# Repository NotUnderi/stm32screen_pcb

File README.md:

# stm32screen

PCB designed to fit into a 52mm closure and interface with some car sensors and stuff

<b>10.6.2026</b>
<br>
Ordered PCBs from JLCPCB. Changed made to previous version pictured below these new ones are disposing of the USB connector entirely and with it, the SP0503BAHTG TVS diode, adding a user switch, Adding better labels on the silkscreen, slightly better layout, disposing of THT caps. The board will be powered straight from the car's battery, this allows easier installation and decreases cost and complexity.

17.3.2026

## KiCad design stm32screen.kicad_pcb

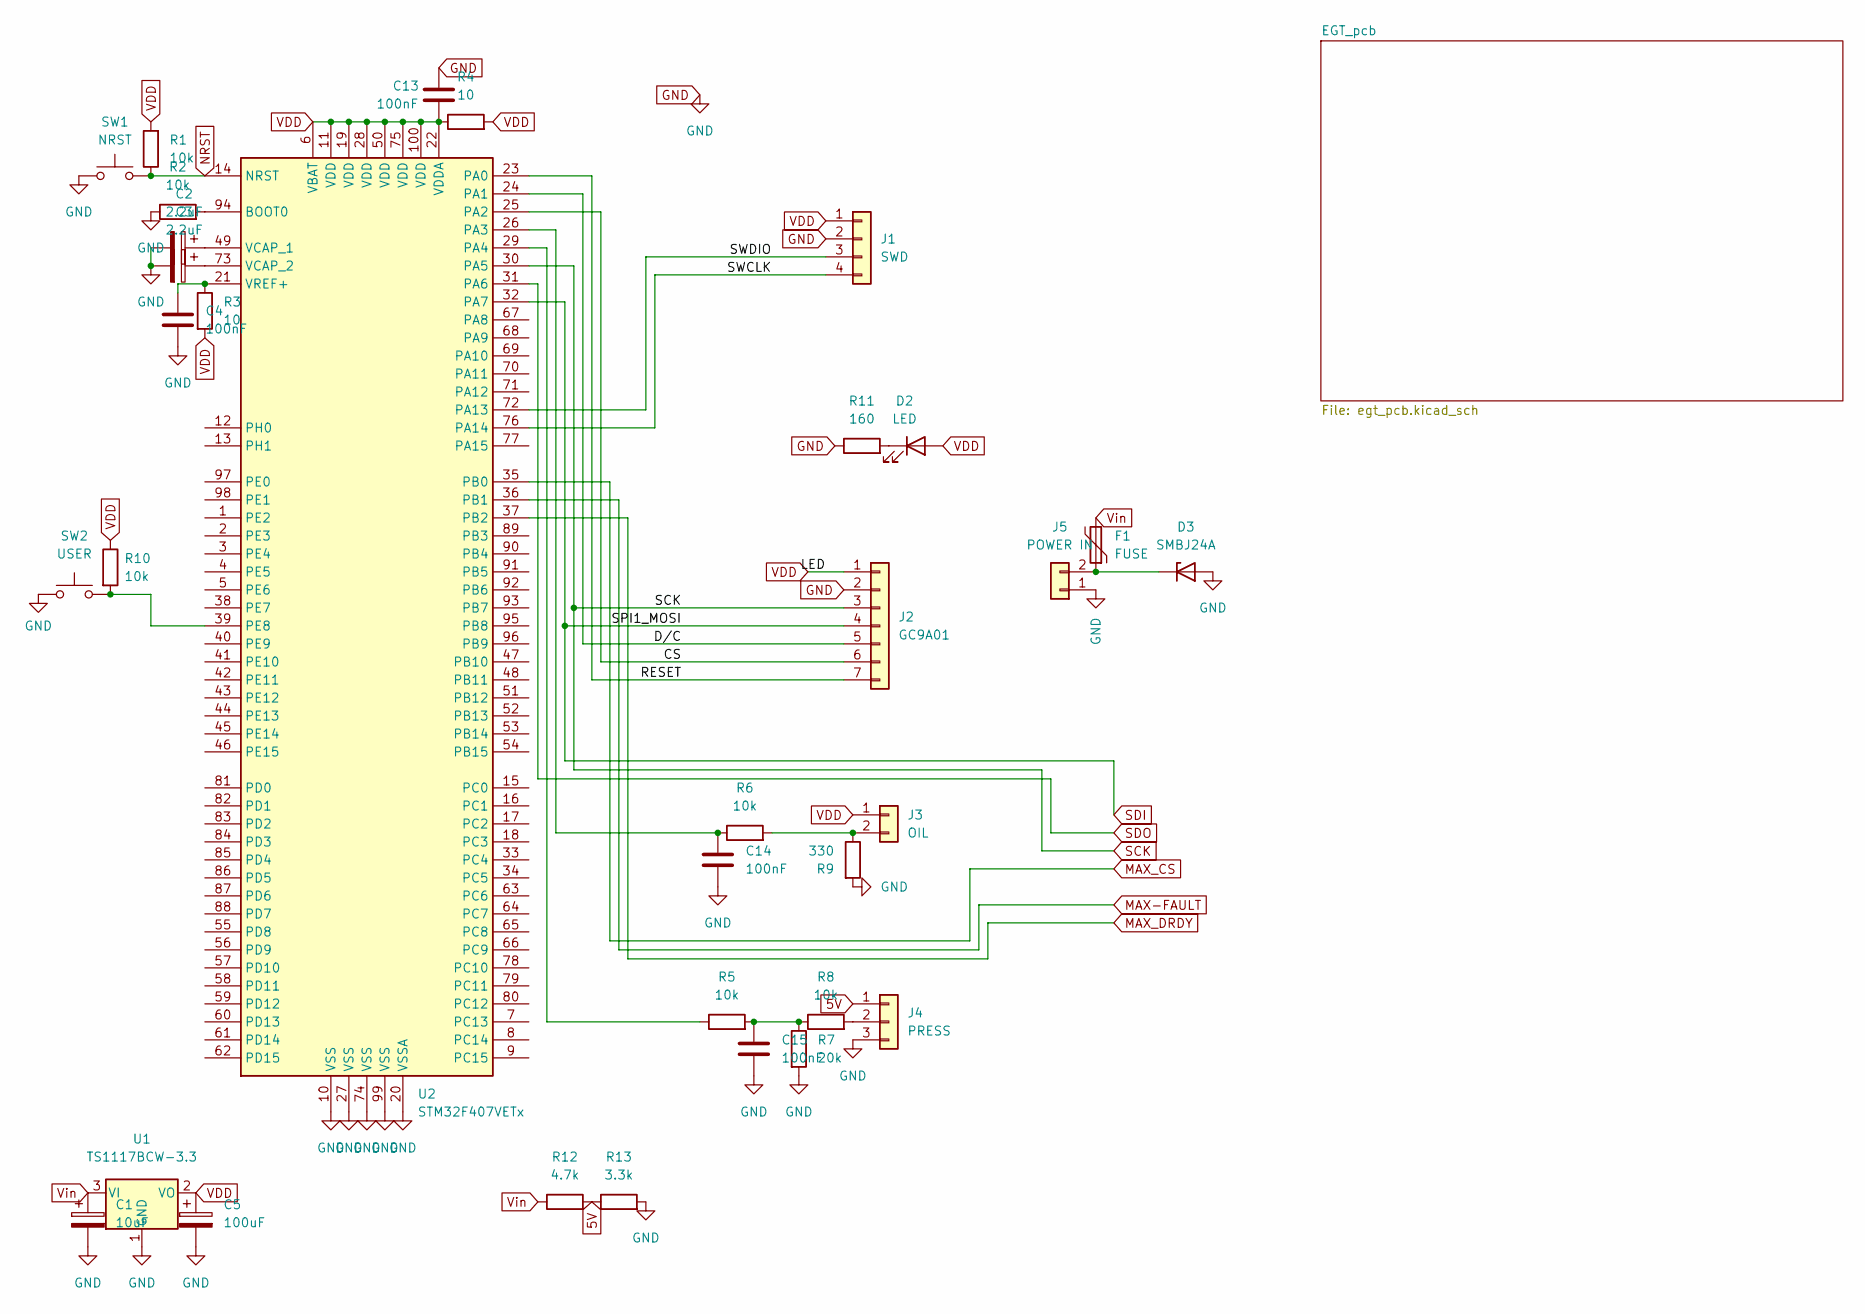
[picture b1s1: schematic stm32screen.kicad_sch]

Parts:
C1: 10uF; C_1210_3225Metric_Pad1.33x2.70mm_HandSolder
C2, C3: 2.2uF; C_1206_3216Metric_Pad1.33x1.80mm_HandSolder
C4, C13, C14, C15: 100nF; C_0805_2012Metric_Pad1.18x1.45mm_HandSolder
C5: 100uF; C_1210_3225Metric_Pad1.33x2.70mm_HandSolder
D2: LED; LED_0603_1608Metric_Pad1.05x0.95mm_HandSolder
D3: SMBJ24A; D_SMB_Handsoldering
F1: FUSE; Fuse_0805_2012Metric_Pad1.15x1.40mm_HandSolder
J1: SWD; PinHeader_1x04_P2.54mm_Vertical
J2: GC9A01; JST_PH_B7B-PH-K_1x07_P2.00mm_Vertical
J3: OIL; JST_XH_B2B-XH-A_1x02_P2.50mm_Vertical
J4: PRESS; JST_XH_B3B-XH-A_1x03_P2.50mm_Vertical
J5: POWER IN; JST_XH_B2B-XH-A_1x02_P2.50mm_Vertical
R1, R2, R5, R6, R8, R10: 10k; R_1218_3246Metric_Pad1.22x4.75mm_HandSolder
R3, R4: 10; R_1218_3246Metric_Pad1.22x4.75mm_HandSolder
R7: 20k; R_0805_2012Metric_Pad1.20x1.40mm_HandSolder
R9: 330; R_0805_2012Metric_Pad1.20x1.40mm_HandSolder
R11: 160; R_0603_1608Metric_Pad0.98x0.95mm_HandSolder
R12: 4.7k; R_0805_2012Metric_Pad1.20x1.40mm_HandSolder
R13: 3.3k; R_0805_2012Metric_Pad1.20x1.40mm_HandSolder
SW1: NRST; SW_Push_1P1T_NO_CK_KSC9xxG
SW2: USER; SW_Push_1P1T_NO_CK_KSC9xxG
U1: TS1117BCW-3.3; SOT-223-3_TabPin2
U2: STM32F407VETx; LQFP-100_14x14mm_P0.5mm

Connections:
5V: J4.1, R12.2, R13.1
/CS: J2.6, U2.25 (PA2)
/D/C: J2.5, U2.24 (PA1)
/RESET: J2.7, U2.23 (PA0)
/SWCLK: J1.4, U2.76 (PA14)
/SWDIO: J1.3, U2.72 (PA13)
GND: C1.2, C2.2, C3.2, C4.2, C5.2, C13.1, C14.2, C15.2, D3.2 (A), J1.2, J2.2, J4.3, J5.1, R2.1, R7.2, R9.2, R11.1, R13.2, SW1.1, SW2.1, U1.1 (GND), U2.10 (VSS), U2.20 (VSSA), U2.27 (VSS), U2.74 (VSS), U2.99 (VSS); also elsewhere on the board
MAX-FAULT: U2.36 (PB1)
MAX_CS: U2.35 (PB0); also elsewhere on the board
MAX_DRDY: U2.37 (PB2); also elsewhere on the board
NRST: R1.1, SW1.2, U2.14 (NRST)
unnamed: C15.1, R5.2, R7.1, R8.1
unnamed: D2.1 (K), R11.2
unnamed: D3.1 (K), F1.1, J5.2
unnamed: J3.2, R6.2, R9.1
unnamed: J4.2, R8.2
unnamed: R2.2, U2.94 (BOOT0)
unnamed: C14.1, R6.1, U2.26 (PA3)
unnamed: R5.1, U2.29 (PA4)
unnamed: R10.2, SW2.2, U2.39 (PE8)
unnamed: C2.1, U2.49 (VCAP_1)
unnamed: C3.1, U2.73 (VCAP_2)
unnamed: C4.1, R3.1, U2.21 (VREF+)
SCK: J2.3, U2.30 (PA5); also elsewhere on the board
SDI: J2.4, U2.32 (PA7); also elsewhere on the board
SDO: U2.31 (PA6); also elsewhere on the board
VDD: C5.1, C13.2, D2.2 (A), J1.1, J2.1, J3.1, R1.2, R3.2, R4.1, R4.2, R10.1, U1.2 (VO), U2.6 (VBAT), U2.11 (VDD), U2.19 (VDD), U2.22 (VDDA), U2.28 (VDD), U2.50 (VDD), U2.75 (VDD), U2.100 (VDD); also elsewhere on the board
Vin: C1.1, F1.2, R12.1, U1.3 (VI)

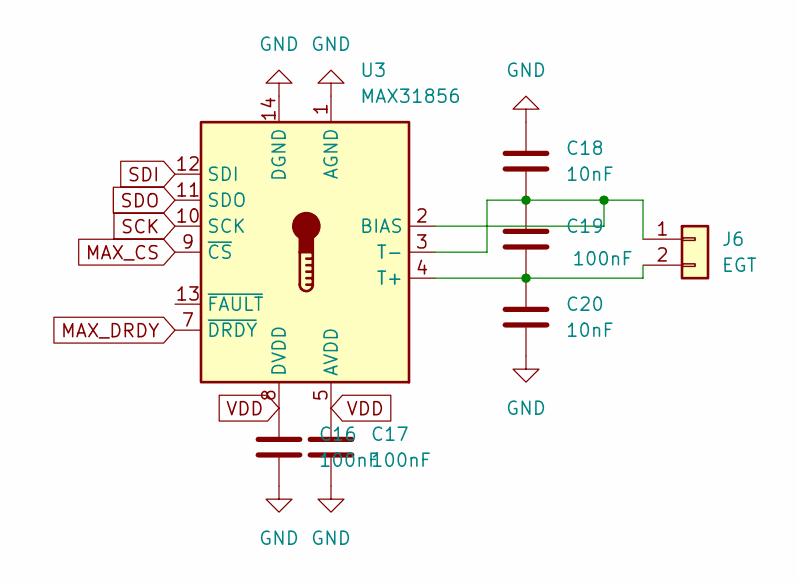
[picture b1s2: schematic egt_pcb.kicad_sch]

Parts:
C16, C17, C19: 100nF; C_0805_2012Metric_Pad1.18x1.45mm_HandSolder
C18, C20: 10nF; C_0805_2012Metric_Pad1.18x1.45mm_HandSolder
J6: EGT; JST_XH_B2B-XH-A_1x02_P2.50mm_Vertical
U3: MAX31856; TSSOP-14_4.4x5mm_P0.65mm

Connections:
GND: C16.1, C17.1, C18.1, C20.2, U3.1 (AGND), U3.14 (DGND); also elsewhere on the board
MAX_CS: U3.9 (~CS); also elsewhere on the board
MAX_DRDY: U3.7 (~DRDY); also elsewhere on the board
unnamed: C18.2, C19.1, J6.1, U3.2 (BIAS), U3.3 (T-)
unnamed: C19.2, C20.1, J6.2, U3.4 (T+)
SCK: U3.10 (SCK); also elsewhere on the board
SDI: U3.12 (SDI); also elsewhere on the board
SDO: U3.11 (SDO); also elsewhere on the board
VDD: C16.2, C17.2, U3.5 (AVDD), U3.8 (DVDD); also elsewhere on the board

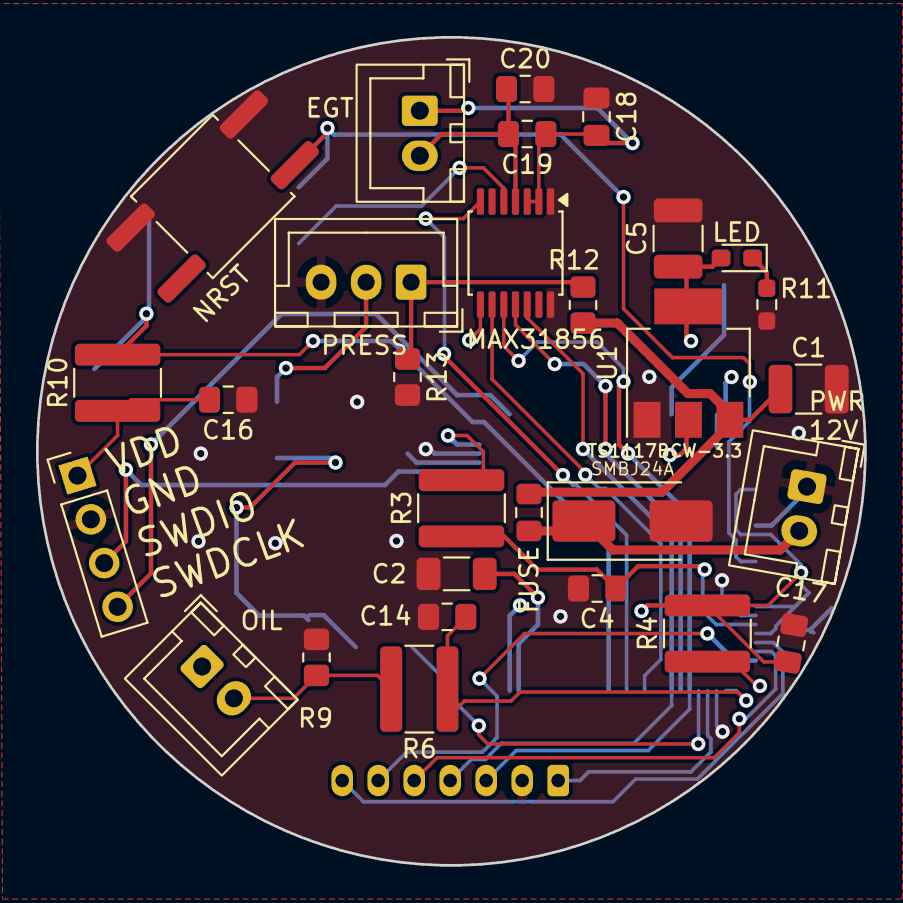
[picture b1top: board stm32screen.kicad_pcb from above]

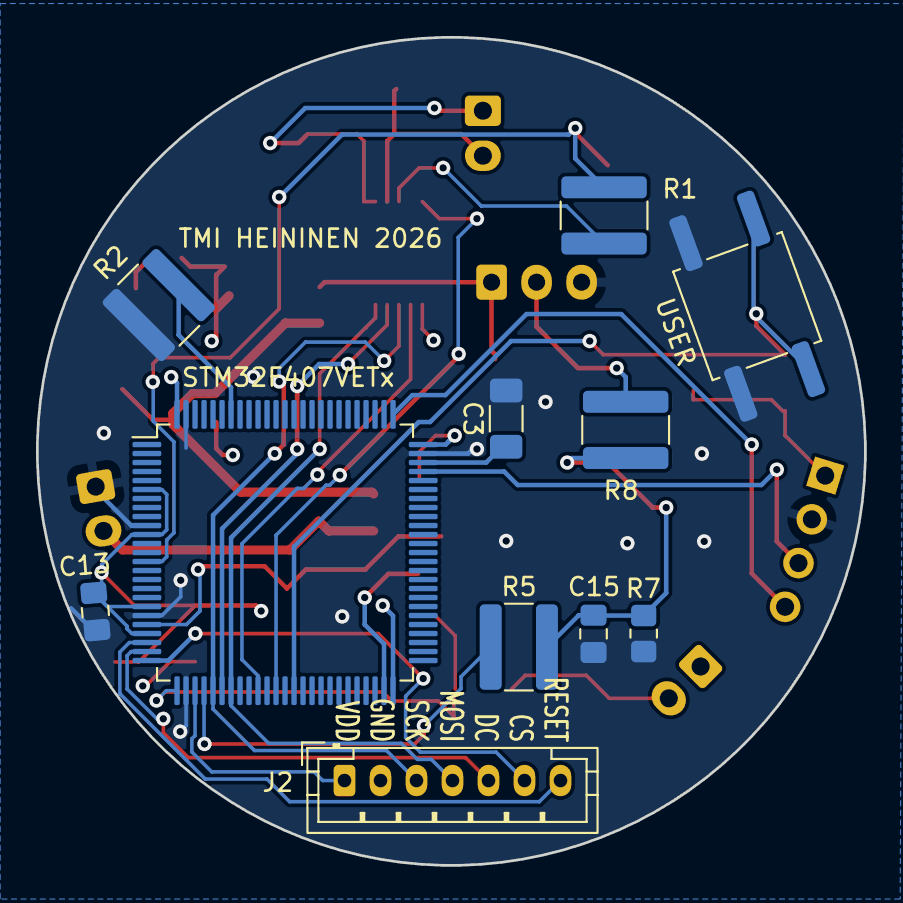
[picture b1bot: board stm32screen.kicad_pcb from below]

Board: 4 copper layers, 46.0 x 46.0 mm, 40 parts (11 on the bottom side), 29 nets.

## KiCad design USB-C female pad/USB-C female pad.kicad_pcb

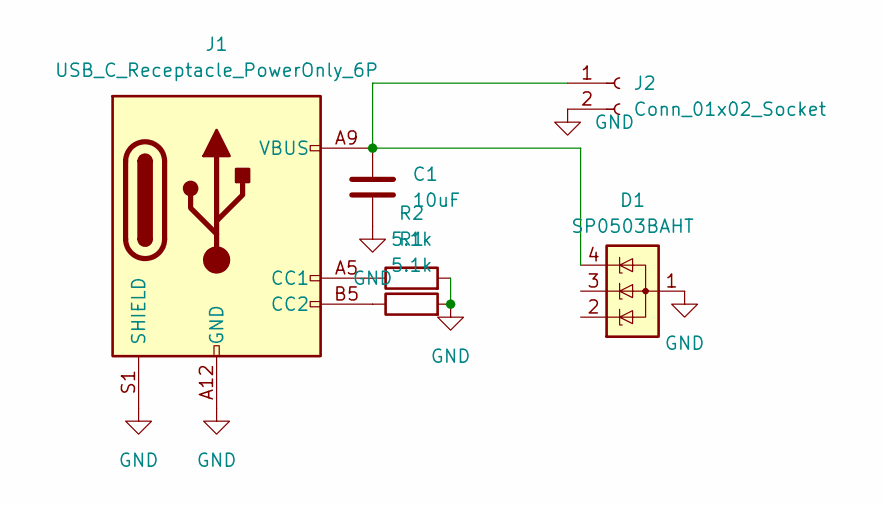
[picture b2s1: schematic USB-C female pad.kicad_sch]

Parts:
C1: 10uF; C_0805_2012Metric_Pad1.18x1.45mm_HandSolder
D1: SP0503BAHT; SOT-143
J1: USB_C_Receptacle_PowerOnly_6P; USB_C_Receptacle_GCT_USB4135-GF-A_6P_TopMnt_Horizontal
J2: Conn_01x02_Socket; PinHeader_1x02_P2.54mm_Vertical
R1, R2: 5.1k; R_2010_5025Metric_Pad1.40x2.65mm_HandSolder

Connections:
GND: C1.2, D1.1 (A), J1.A12 (GND), J1.B12 (GND), J1.S1 (SHIELD), J2.2, R1.2, R2.2
unnamed: J1.A5 (CC1), R2.1
unnamed: J1.B5 (CC2), R1.1
unnamed: C1.1, D1.4 (K), J1.A9 (VBUS), J1.B9 (VBUS), J2.1

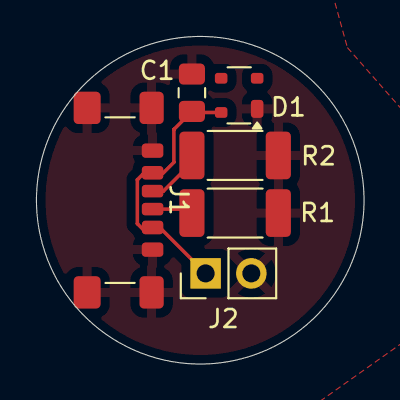
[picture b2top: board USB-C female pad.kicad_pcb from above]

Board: 2 copper layers, 18.2 x 18.2 mm, 6 parts (0 on the bottom side), 4 nets.

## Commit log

2026-03-12 Init
2026-03-12 Added a readme
2026-03-12 Roughing out the PCB.
2026-03-12 Routed rest of the unconnected pads
2026-03-16 Added a status LED
2026-03-17 Optimized PCB layout. Added images
2026-03-17 Update README with PCB images
    Added date and images of the STM32screen PCB.
2026-04-01 Added STL files for the first iteration of cases
2026-04-01 Changed PCB size to 23mm radius, rearranged parts to fit
2026-04-01 Connected a couple of unconnected pads
2026-04-01 Fixed clipping silkscreen
2026-04-01 Created a small USB-C PCB to provide portable power on bench
2026-04-02 Small trace changes
2026-04-16 A bit neater layout. Add missing parts to PCB. Refine silkscreen. New screenshots
2026-04-16 THT caps to MLCC as per TS1117B datasheet. STM32 ref caps as well
2026-04-16 Adjusted silkscreen and component layout, changed some component values so that silkscreen doesn't change every time
2026-05-25 Add voltage divider for 5v if using 12v in
2026-05-25 Add SP0503BAHTG to USB-C pad
2026-05-25 Changed footprints to larger ones and for general unity of footprints
2026-05-25 Add BOM with Mouser part numbers
2026-05-25 Fix missing ground connection for MAX31856
2026-05-28 Changed display conn symbol, added NC flags. Corrected silkscreen labels
2026-05-29 Switched from SP0503BAHT to SMBJ24A for a TVS Diode, since we're using 12v supply now instead of 5v
2026-06-07 Ground pour spacing 0.2mm, small trace fixes.
2026-06-10 Plot folder changed to project specific. Added pictures of new PCB
2026-06-10 Updated README, changed pictures to jpg
2026-06-10 Fixed typo in readme
